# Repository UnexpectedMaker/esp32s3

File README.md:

# Unexpected Maker - ESP32-S3 Boards 

Assorted files for my ESP32-S3 development boards 

You can find out more about my ESP32-S3 boards at https://esp32s3.com 

# Contents
In this repo you'll find the following items:

## 3D Models
3D STEP files for each of the OMGS3, NanoS3, TinyS3, ProS3 and FeatherS3 boards

## KiCAD 6/7/8 Symbols
KiCAD 6 symbol files for each of the boards that you can use when integrating one of them into one of your PCB designs.
NanoS3 symbol file is for KiCAD 7 or later
OMGS3 symbol file is for KiCAD 8 or later

## KiCAD 6/7 Footprints	
KiCAD 6 footprint files for each of the boards including both SMD and TH versions for the ProS3
NanoS3 footprint file is for KiCAD 7 or later
OMGS3 footprint file is for KiCAD 8 or later

## Schematics
PDF Schematics for each of the OMGS3, NanoS3, TinyS3, ProS3 and FeatherS3 boards

## Pin Reference Cards
Hires pinout reference cards for each of the OMGS3, NanoS3, TinyS3, ProS3 and FeatherS3 boards

# Support Unexpected Maker

I love designing, making, and releasing projects and products that empower others to learn and build amazing things! I do it because I believe it’s important to share knowledge and give back to the community as many have done before me. It helps us all learn and grow.

Please consider supporting me by buying some of my products from:

https://unexpectedmaker.com/shop

Or by buying one of my products on tindie or Lectronz:

https://www.tindie.com/stores/seonr/
https://lectronz.com/stores/unexpectedmaker

Or by becoming a Patron:

https://www.patreon.com/unexpectedmaker

## Unexpected Maker
http://youtube.com/c/unexpectedmaker

http://twitter.com/unexpectedmaker

https://discord.gg/xAHpApP

https://www.facebook.com/unexpectedmaker/

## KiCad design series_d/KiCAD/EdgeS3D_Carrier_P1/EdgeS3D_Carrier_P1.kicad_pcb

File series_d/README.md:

# Unexpected Maker - Series[D]

Assorted files for my new ESP32-S3 Series[D] development boards 

You can find out more about my ESP32-S3 boards at https://esp32s3.com

# Contents
In this repo you'll find the following items:

## 3D Models
3D STEP files for each of the TinyS3[D], ProS3[D], FeatherS3[D] and EdgeS3[D] boards

You'll also find a STEP file for the EdgeS3[D] Reference Carrier board and a STEP for the M.2 connector footprint with the EdgeS3[D] inserted to help line things up.

## Schematics
PDF Schematics for each of the TinyS3[D], ProS3[D], FeatherS3[D] and EdgeS3[D] boards.

## KiCAD (v9)
Symbol and Footprint for EdgeS3[D] and a project folder for the EdgeS3[D] Reference Carrier PCB.

## Pin Reference Cards
Hires pinout reference cards for each of the TinyS3[D], ProS3[D], FeatherS3[D] and EdgeS3[D] boards

# Support Unexpected Maker
I love designing, making, and releasing projects and products that empower others to learn and build amazing things! I do it because I believe it’s important to share knowledge and give back to the community as many have done before me. It helps us all learn and grow.

Please consider supporting me by buying some of my products from:

https://unexpectedmaker.com/shop

Or by buying one of my products on tindie or Lectronz:

https://www.tindie.com/stores/seonr/
https://lectronz.com/stores/unexpectedmaker

Or by becoming a Patron:

https://www.patreon.com/unexpectedmaker

## Unexpected Maker
http://youtube.com/c/unexpectedmaker

http://twitter.com/unexpectedmaker

https://discord.gg/xAHpApP

https://www.facebook.com/unexpectedmaker/

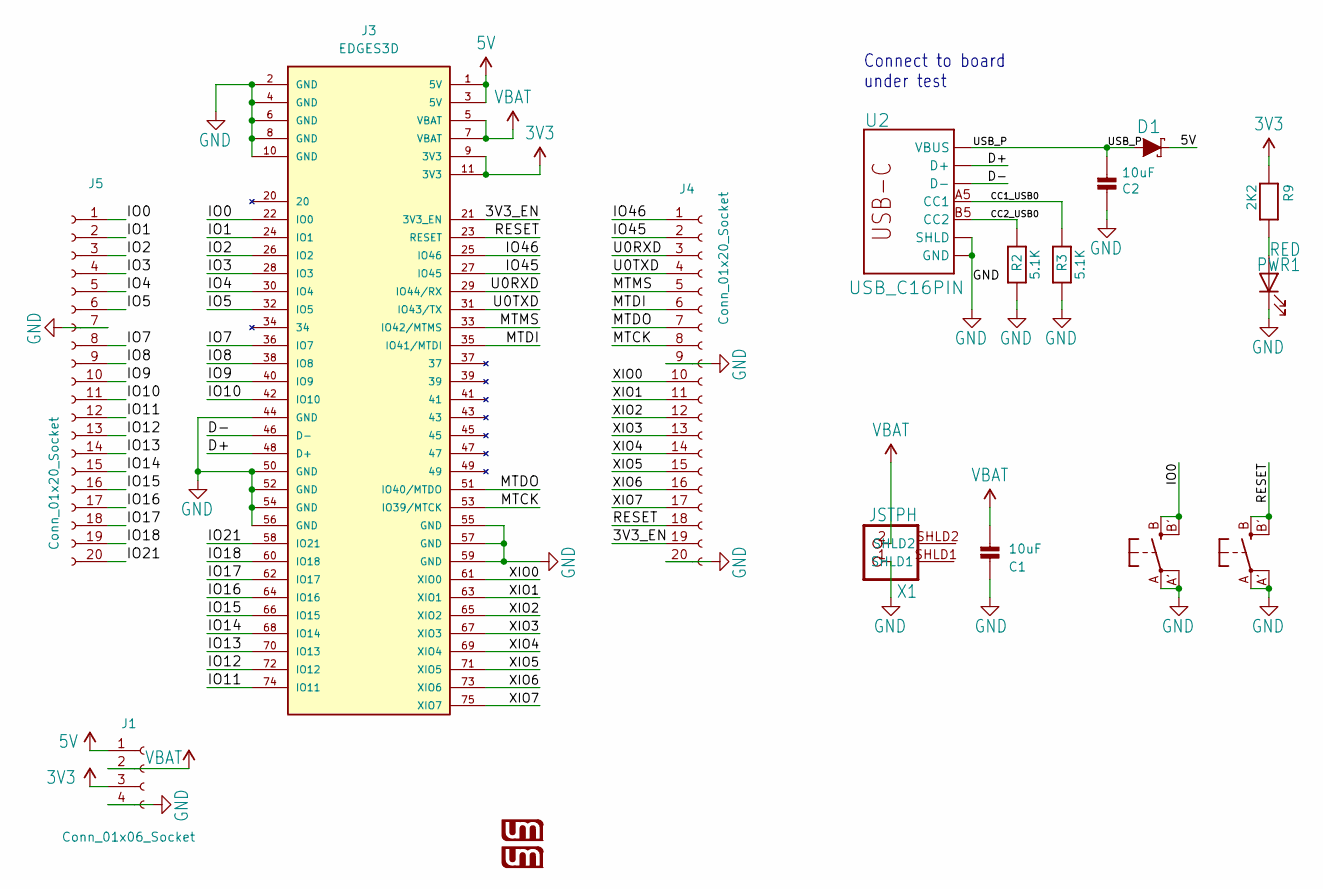
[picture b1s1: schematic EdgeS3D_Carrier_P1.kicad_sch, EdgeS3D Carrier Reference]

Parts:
C1, C2: 10uF; C_0603_1608Metric
D1: DIODE-SCHOTTKYWIDE; SOD-523-MSK4010
J1: Conn_01x06_Socket; PinHeader_1x04_P2.54mm_Vertical
J3: EDGES3D; AMPHENOL_MDT275B03001; PARTREV 7
J4, J5: Conn_01x20_Socket; PinHeader_1x20_P2.54mm_Vertical
PWR1: RED; LED_0805_2012Metric
R2, R3: 5.1K; R_0402_1005Metric
R9: 2K2; _0805MP
SW1, SW2: KMR2; BTN_KMR2_4.6X2.8
U2: USB_C16PIN; USB-C-16P-LESSPASTE-2-FIxed
U$1, U$2: UM_LOGONEW_SMALL; UM_LOGO_NEW_SMALL
X1: JSTPH; JST-PICOBLADE

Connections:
3V3: J1.3, J3.9 (3V3), J3.11 (3V3), R9.1
5V: D1.C, J1.1, J3.1 (5V), J3.3 (5V)
/3V3_EN: J3.21 (3V3_EN), J4.19
/CC1_USB0: R3.2, U2.A5 (CC1)
/CC2_USB0: R2.2, U2.B5 (CC2)
/D+: J3.48 (D+), U2.A6 (D+), U2.B6 (D+)
/D-: J3.46 (D-), U2.A7 (D-), U2.B7 (D-)
/IO0: J3.22 (IO0), J5.1, SW1.B (S), SW1.B' (S1)
/IO1: J3.24 (IO1), J5.2
/IO2: J3.26 (IO2), J5.3
/IO3: J3.28 (IO3), J5.4
/IO4: J3.30 (IO4), J5.5
/IO5: J3.32 (IO5), J5.6
/IO7: J3.36 (IO7), J5.8
/IO8: J3.38 (IO8), J5.9
/IO9: J3.40 (IO9), J5.10
/IO10: J3.42 (IO10), J5.11
/IO11: J3.74 (IO11), J5.12
/IO12: J3.72 (IO12), J5.13
/IO13: J3.70 (IO13), J5.14
/IO14: J3.68 (IO14), J5.15
/IO15: J3.66 (IO15), J5.16
/IO16: J3.64 (IO16), J5.17
/IO17: J3.62 (IO17), J5.18
/IO18: J3.60 (IO18), J5.19
/IO21: J3.58 (IO21), J5.20
/IO45: J3.27 (IO45), J4.2
/IO46: J3.25 (IO46), J4.1
/MTCK: J3.53 (IO39/MTCK), J4.8
/MTDI: J3.35 (IO41/MTDI), J4.6
/MTDO: J3.51 (IO40/MTDO), J4.7
/MTMS: J3.33 (IO42/MTMS), J4.5
/RESET: J3.23 (RESET), J4.18, SW2.B (S), SW2.B' (S1)
/U0RXD: J3.29 (IO44/RX), J4.3
/U0TXD: J3.31 (IO43/TX), J4.4
/USB_P: C2.2, D1.A, U2.VBUS1 (VBUS), U2.VBUS2 (VBUS)
/XIO0: J3.61 (XIO0), J4.10
/XIO1: J3.63 (XIO1), J4.11
/XIO2: J3.65 (XIO2), J4.12
/XIO3: J3.67 (XIO3), J4.13
/XIO4: J3.69 (XIO4), J4.14
/XIO5: J3.71 (XIO5), J4.15
/XIO6: J3.73 (XIO6), J4.16
/XIO7: J3.75 (XIO7), J4.17
GND: C1.1, C2.1, J1.4, J3.2 (GND), J3.4 (GND), J3.6 (GND), J3.8 (GND), J3.10 (GND), J3.44 (GND), J3.50 (GND), J3.52 (GND), J3.54 (GND), J3.55 (GND), J3.56 (GND), J3.57 (GND), J3.59 (GND), J4.9, J4.20, J5.7, PWR1.1 (K), R2.1, R3.1, SW1.A, SW1.A' (P1), SW2.A, SW2.A' (P1), U2.GND, U2.GND2 (GND), U2.SHLD, U2.SHLD2 (SHLD), U2.SHLD3 (SHLD), U2.SHLD4 (SHLD), U2.SHLD5 (SHLD), U2.SHLD6 (SHLD), U2.SHLD7 (SHLD), U2.SHLD8 (SHLD), X1.1
unnamed: PWR1.2 (A), R9.2
VBAT: C1.2, J1.2, J3.5 (VBAT), J3.7 (VBAT), X1.2

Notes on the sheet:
Connect to board under test

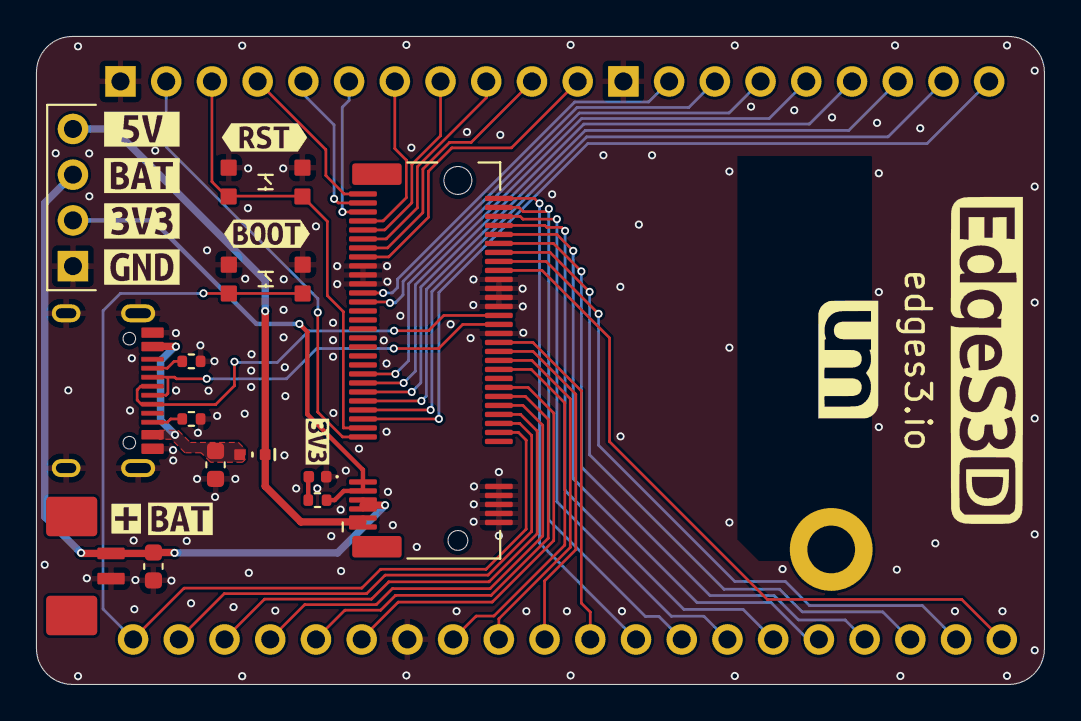
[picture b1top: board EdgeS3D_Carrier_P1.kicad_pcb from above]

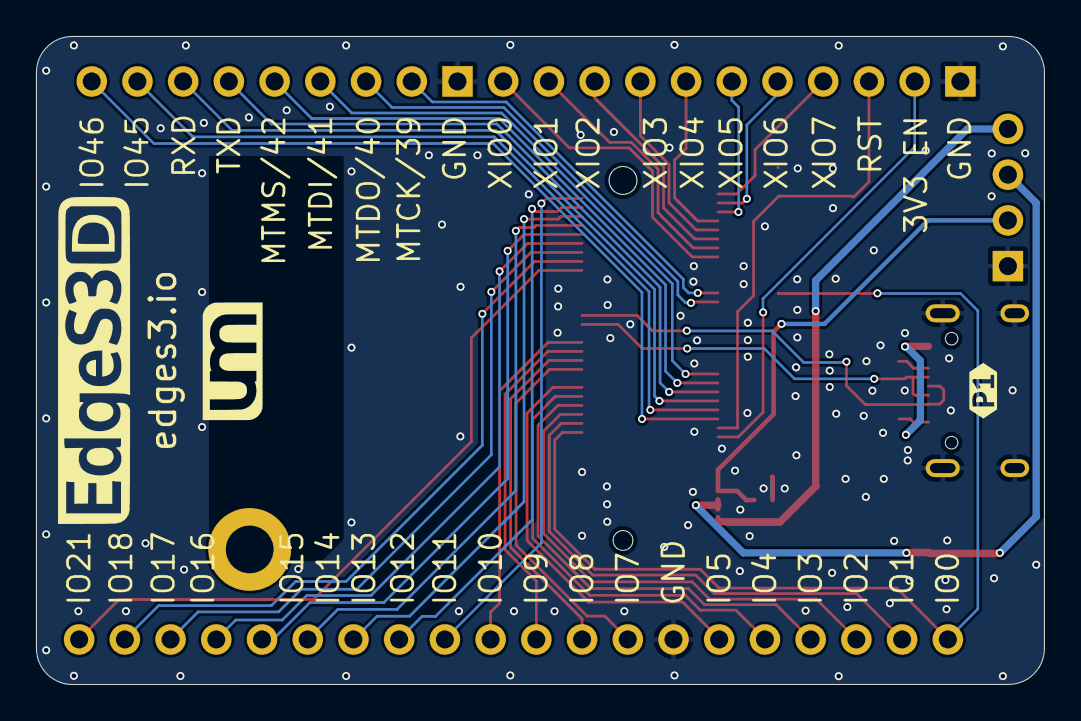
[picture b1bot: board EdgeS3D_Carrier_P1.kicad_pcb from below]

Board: 2 copper layers, 56.0 x 36.0 mm, 27 parts (2 on the bottom side), 47 nets.

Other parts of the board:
kibuzzard-66BFF55A: G***; kibuzzard-66BFF55A
kibuzzard-66BFF56B: G***; kibuzzard-66BFF56B
kibuzzard-66C05786: G***; kibuzzard-66C05786
kibuzzard-6857AC6A: G***; kibuzzard-6857AC6A
kibuzzard-6857AC7B: G***; kibuzzard-6857AC7B
kibuzzard-6857AC8E: G***; kibuzzard-6857AC8E
kibuzzard-6857AC89: G***; kibuzzard-6857AC89
kibuzzard-6857AD16: G***; kibuzzard-6857AD16
kibuzzard-6857ADA7: G***; kibuzzard-6857ADA7
kibuzzard-664315DB: G***; kibuzzard-664315DB

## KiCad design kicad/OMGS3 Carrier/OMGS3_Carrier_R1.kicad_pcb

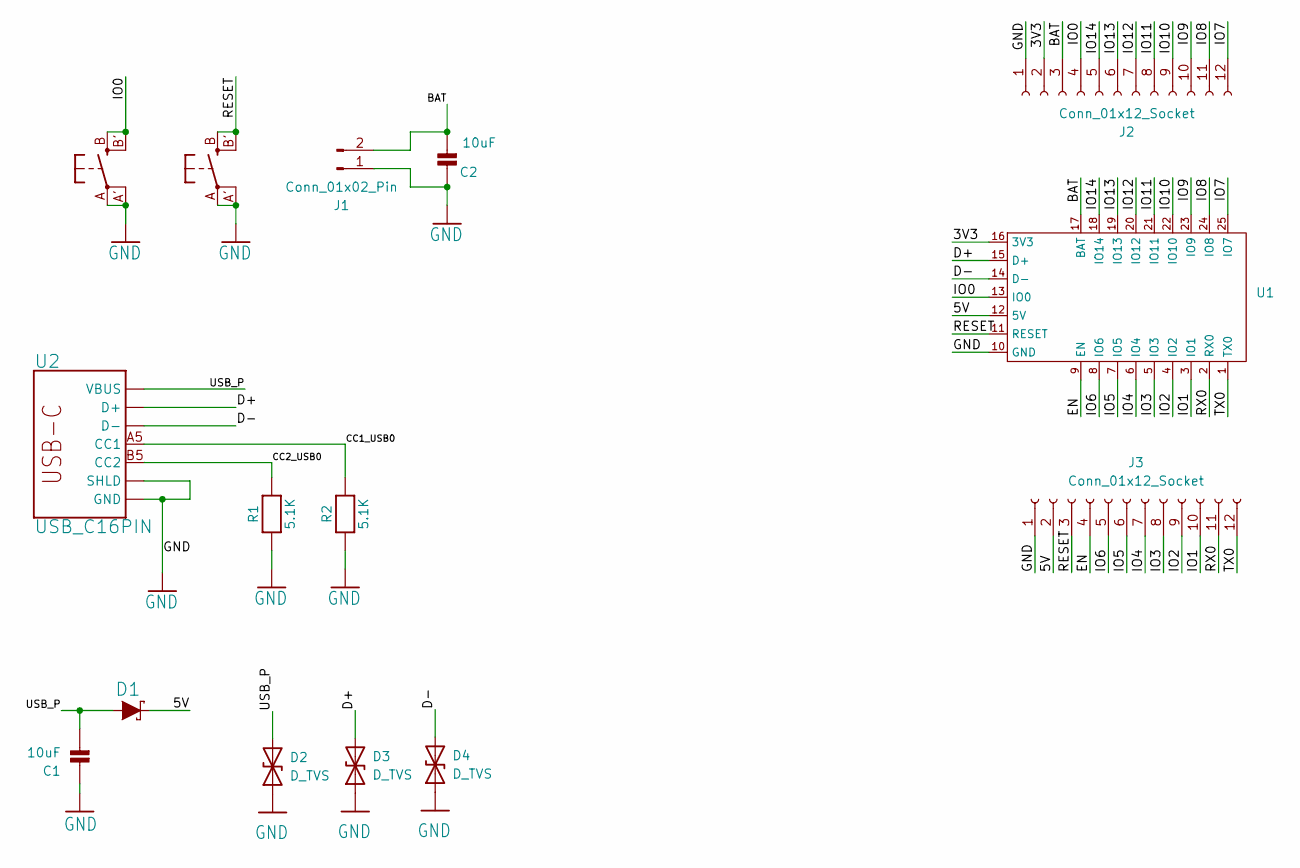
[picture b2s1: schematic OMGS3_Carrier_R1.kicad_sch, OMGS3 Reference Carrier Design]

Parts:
C1, C2: 10uF; C_0603_1608Metric
D1: DIODE-SCHOTTKYWIDE; SOD-523-MSK4010
D2, D3, D4: D_TVS; X1-DFN1006-2
J1: Conn_01x02_Pin; JST-PICOBLADE
J2, J3: Conn_01x12_Socket; PinHeader_1x12_P2.54mm_Vertical
R1, R2: 5.1K; R_0402_1005Metric
SW1, SW2: KMR2; BTN_KMR2_4.6X2.8
U1: OMGS3
U2: USB_C16PIN; USB-C-16P-LESSPASTE-2-Fixed-Sqr-Front

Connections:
/3V3: J2.2, U1.16 (3V3)
/5V: D1.C, J3.2, U1.12 (5V)
/BAT: C2.2, J1.2, J2.3, U1.17 (BAT)
/CC1_USB0: R2.2, U2.A5 (CC1)
/CC2_USB0: R1.2, U2.B5 (CC2)
/D+: D3.2 (A2), U1.15 (D+), U2.A6 (D+), U2.B6 (D+)
/D-: D4.2 (A2), U1.14 (D-), U2.A7 (D-), U2.B7 (D-)
/EN: J3.4, U1.9 (EN)
/IO0: J2.4, SW1.B (S), SW1.B' (S1), U1.13 (IO0)
/IO1: J3.10, U1.3 (IO1)
/IO2: J3.9, U1.4 (IO2)
/IO3: J3.8, U1.5 (IO3)
/IO4: J3.7, U1.6 (IO4)
/IO5: J3.6, U1.7 (IO5)
/IO6: J3.5, U1.8 (IO6)
/IO7: J2.12, U1.25 (IO7)
/IO8: J2.11, U1.24 (IO8)
/IO9: J2.10, U1.23 (IO9)
/IO10: J2.9, U1.22 (IO10)
/IO11: J2.8, U1.21 (IO11)
/IO12: J2.7, U1.20 (IO12)
/IO13: J2.6, U1.19 (IO13)
/IO14: J2.5, U1.18 (IO14)
/RESET: J3.3, SW2.B (S), SW2.B' (S1), U1.11 (RESET)
/RX0: J3.11, U1.2 (RX0)
/TX0: J3.12, U1.1 (TX0)
/USB_P: C1.2, D1.A, D2.2 (A2), U2.VBUS1 (VBUS), U2.VBUS2 (VBUS)
GND: C1.1, C2.1, D2.1 (A1), D3.1 (A1), D4.1 (A1), J1.1, J2.1, J3.1, R1.1, R2.1, SW1.A, SW1.A' (P1), SW2.A, SW2.A' (P1), U1.10 (GND), U1.EXP, U2.GND, U2.GND2 (GND), U2.SHLD, U2.SHLD1 (SHLD), U2.SHLD2 (SHLD), U2.SHLD3 (SHLD), U2.SHLD4 (SHLD), U2.SHLD5 (SHLD), U2.SHLD6 (SHLD), U2.SHLD7 (SHLD), U2.SHLD8 (SHLD)

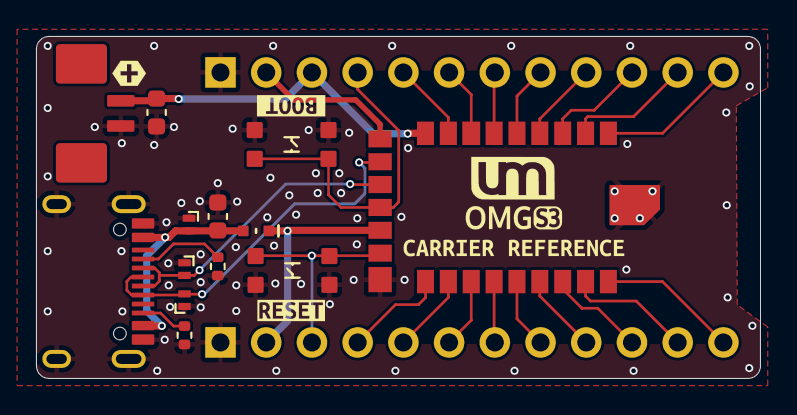
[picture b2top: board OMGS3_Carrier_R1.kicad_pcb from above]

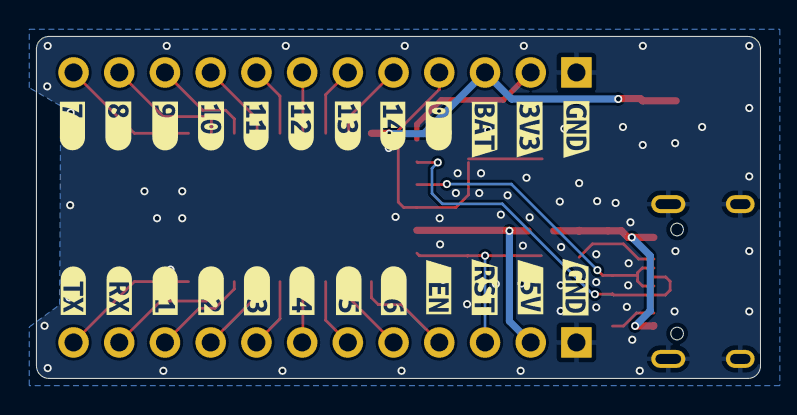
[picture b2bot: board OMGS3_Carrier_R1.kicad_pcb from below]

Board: 2 copper layers, 40.2 x 19.0 mm, 43 parts (24 on the bottom side), 28 nets.

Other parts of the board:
kibuzzard-66A337D7: G***; kibuzzard-66A337D7
kibuzzard-66A3379E: G***; kibuzzard-66A3379E
kibuzzard-66BFF9CC: G***; kibuzzard-66BFF9CC
kibuzzard-66BFF9DF: G***; kibuzzard-66BFF9DF
kibuzzard-66BFF9E6: G***; kibuzzard-66BFF9E6
kibuzzard-66BFF9F3: G***; kibuzzard-66BFF9F3
kibuzzard-66BFF9F9: G***; kibuzzard-66BFF9F9
kibuzzard-66BFF9FE: G***; kibuzzard-66BFF9FE
kibuzzard-66BFFA1D: G***; kibuzzard-66BFFA1D
kibuzzard-66BFFA03: G***; kibuzzard-66BFFA03
kibuzzard-66BFFA07: G***; kibuzzard-66BFFA07
kibuzzard-66BFFA15: G***; kibuzzard-66BFFA15
kibuzzard-66BFFA19: G***; kibuzzard-66BFFA19
kibuzzard-66BFFA21: G***; kibuzzard-66BFFA21
kibuzzard-66BFFAE0: G***; kibuzzard-66BFFAE0
kibuzzard-66BFFAF9: G***; kibuzzard-66BFFAF9
kibuzzard-66BFFB0C: G***; kibuzzard-66BFFB0C
kibuzzard-66BFFB4C: G***; kibuzzard-66BFFB4C
kibuzzard-66BFFB4F: G***; kibuzzard-66BFFB4F
kibuzzard-66BFFB5D: G***; kibuzzard-66BFFB5D
kibuzzard-66BFFB12: G***; kibuzzard-66BFFB12
kibuzzard-66BFFB21: G***; kibuzzard-66BFFB21
kibuzzard-66BFFB47: G***; kibuzzard-66BFFB47
kibuzzard-66BFFB52: G***; kibuzzard-66BFFB52
kibuzzard-66BFFB54: G***; kibuzzard-66BFFB54
kibuzzard-66BFFB58: G***; kibuzzard-66BFFB58
kibuzzard-66C531C2: G***; kibuzzard-66C531C2
kibuzzard-66C53217: G***; kibuzzard-66C53217

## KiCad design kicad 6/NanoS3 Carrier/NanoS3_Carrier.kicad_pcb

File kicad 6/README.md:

# KiCAD Footprints - Unexpected Maker - ESP32-S3 Boards 
KiCAD Footprints for my ESP32-S3 boards  

You can find out more about my ESP32-S3 boards at https://esp32s3.com 

Please refer to the included license.

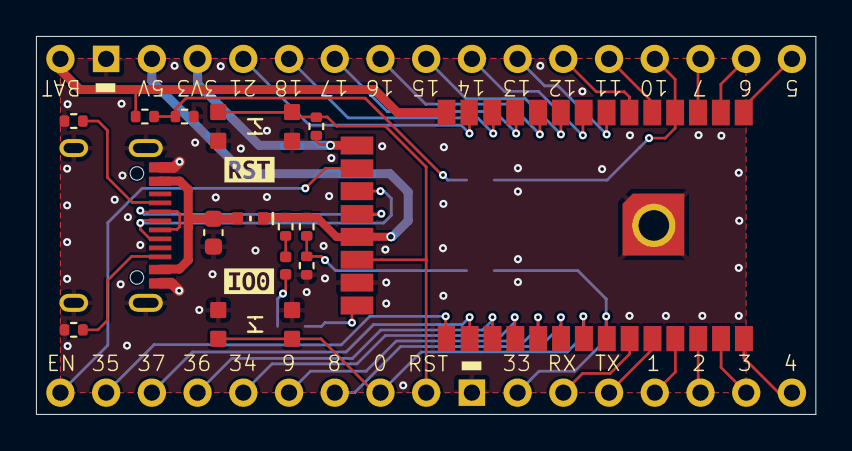
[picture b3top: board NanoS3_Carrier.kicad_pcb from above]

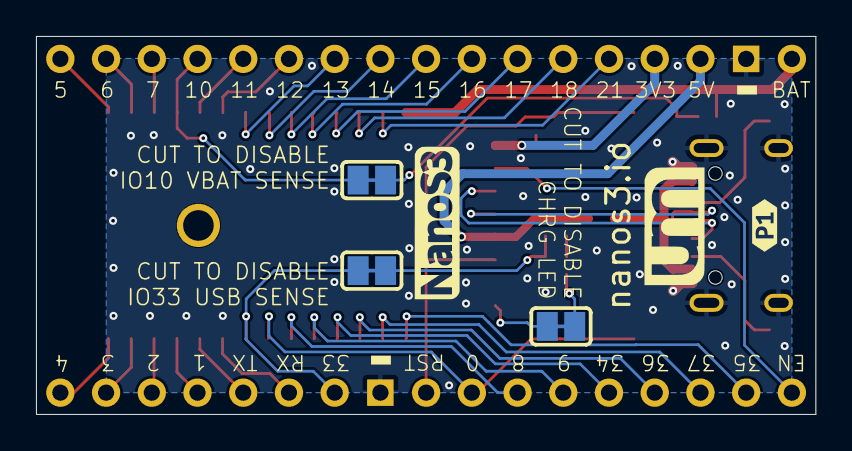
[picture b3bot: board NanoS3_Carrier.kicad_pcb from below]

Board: 2 copper layers, 43.3 x 21.0 mm, 24 parts (5 on the bottom side), 43 nets.

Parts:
A1, A2, A3: SOLDERJUMPERCLOSED; SOLDERJUMPER_CLOSEDWIRE
C1: C_Small; C_0603_1608Metric
D3: ORANGE; LED_0402_1005Metric
D5: DIODE-SCHOTTKYWIDE; SOD-523-MSK4010
J2: USB_C; USB-C-16P-LESSPASTE-2-FIxed
J4, J5: Conn_01x17_Pin; 1X17_BLIZZARD_S3_BOTTOM
R1: 2K; R_0402_1005Metric
R2: 2K2; R_0402_1005Metric
R3: 3K3; R_0402_1005Metric
R6: 442K; R_0402_1005Metric
R7: 160K; R_0402_1005Metric
R9, R11: 5.1K; R_0402_1005Metric
R14: 10K; R_0402_1005Metric
SW1, SW2: SWITCH_TACT_SMT4.6X2.8; BTN_KMR2_4.6X2.8
U1: NanoS3; NanoS3_HandSolder
U$88: UM_LOGONEW_SMALLER; UM_LOGO_NEW_SMALL
kibuzzard-649F567F: G***; kibuzzard-649F567F
kibuzzard-649F677A: G***; kibuzzard-649F677A
kibuzzard-649F5696: G***; kibuzzard-649F5696

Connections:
3.3V: J4.4, R14.2, U1.8 (3v3)
/CC1: J2.A5 (CC1), R11.2
/CC2: J2.B5 (CC2), R9.2
/D+: J2.A6 (D+), J2.B6 (D+), U1.6 (D+)
/D-: J2.A7 (D-), J2.B7 (D-), U1.5 (D-)
/EN: J5.1, U1.7 (EN)
/IO0: J5.8, SW2.A, SW2.A' (P1), U1.29 (IO0)
/IO1: J5.14, U1.33 (IO1)
/IO2: J5.15, U1.34 (IO2)
/IO3: J5.16, U1.35 (IO3)
/IO4: J5.17, U1.36 (IO4)
/IO5: J4.17, U1.22 (IO5)
/IO6: J4.16, U1.21 (IO6)
/IO7: J4.15, U1.20 (IO7)
/IO8: J5.7, U1.28 (IO8)
/IO9: J5.6, U1.27 (IO9)
/IO10: A2.1, J4.14, U1.19 (IO10)
/IO10_JUMPER: A2.2, R6.2, R7.1
/IO11: J4.13, U1.18 (IO11)
/IO12: J4.12, U1.17 (IO12)
/IO13: J4.11, U1.16 (IO13)
/IO14: J4.10, U1.15 (IO14)
/IO15: J4.9, U1.14 (IO15)
/IO16: J4.8, U1.13 (IO16)
/IO17: J4.7, U1.12 (IO17)
/IO18: J4.6, U1.11 (IO18)
/IO21: J4.5, U1.10 (IO21)
/IO33: A1.1, J5.11, U1.30 (IO33)
/IO33_JUMPER: A1.2, R2.2, R3.1
/IO34: J5.5, U1.26 (IO34)
/IO35: J5.2, U1.23 (IO35)
/IO36: J5.4, U1.25 (IO36)
/IO37: J5.3, U1.24 (IO37)
/RESET: J5.9, R14.1, SW1.A, SW1.A' (P1), U1.3 (RESET)
/RX: J5.12, U1.31 (RX)
/STAT: A3.2, U1.1 (STAT)
/STAT_JUMPER: A3.1, D3.2
/TX: J5.13, U1.32 (TX)
/USB: D5.C, J4.3, R1.1, R2.1, U1.4 (5V)
/USB_P: C1.2, D5.A, J2.VBUS1 (VBUS), J2.VBUS2 (VBUS)
GND: C1.1, J2.GND, J2.GND2 (GND), J2.SHLD1 (SHLD), J2.SHLD2 (SHLD), J2.SHLD3 (SHLD), J2.SHLD4 (SHLD), J4.2, J5.10, R3.2, R7.2, R9.1, R11.1, SW1.B (S), SW1.B' (S1), SW2.B (S), SW2.B' (S1), U1.2 (GND)
unnamed: D3.1, R1.2
VBAT: J4.1, R6.1, U1.9 (VBAT)

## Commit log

2022-01-30 Initial content commit
2022-02-02 Updated MicroPython firmware as at Feb 2nd, 20212 Added helper libraries and example code for MicroPython
2022-02-03 Fixed some typos, thanks @mcauser
2022-02-26 Neopixels are GRB order
2022-02-28 update get_battery_voltage with clear calculation
2022-03-15 Added newer MicroPython nightly builds and removed older ones
2022-04-23 Updated FeatherS3 pinout card to latest version
2022-04-24 RGB-Blink sample
2022-04-24 RGB-Blink sample for all 3 boards
2022-04-24 RGB-Blink brightness
2022-04-25 README files added
2022-04-25 Rainbox ColorWheel sample
2022-04-28 Added link to the Arduino Helper Library repository
2022-05-23 Fixed ProS3 symbol pin orientations
2022-08-06 Updated ProS3 and FeatherS3 schematics, fixing vertical STEMMA connector pin names
2022-08-06 Fixed STEMMA/QT signal orientation to stop confusing people :)
2022-08-17 Updated readme and removed old MP 1.18 firmware
2022-09-21 Update README.md
    Fixed incorrect examples URL
2022-12-24 Fixed incorrectly rotated pins on the TinyS3 and FeatherS3 KiCAD Symbol
2023-01-14 Update README.md
    added exact helper library name
2023-03-01 Updated ProS3 Symbol with aligned pins for better grid mapping
2023-03-11 Updated FeatherS3 schematic for P7 to show new IO pins for I2C bus 2 on the vertical STEMMA/QT connector
2023-07-26 Added KiCAD 7 Footprint and Symbol for NanoS3
2023-07-26 Added KiCAD 7 NanoS3 Carrier Design Files
2023-07-27 Added NanoS3 Schematic
2023-07-29 Fixed incorrect NanoS3 KiCAD Symbol and added missing pinout card
2023-08-02 Updated TinyS3 models
2023-08-02 Updated other ESP32-S3 models
2023-08-02 Readme changes
2023-08-02 Updated kicad folder
2023-08-02 making images smaller
2023-08-02 make images smaller
2023-08-26 Updated pinout cards and added uFL versions
2024-02-08 Updated FeatherS3 pinout cards to include ADC info for VBAT Sense and AMB Light Sensor
2024-03-18 Fixed grid spacing for KiCAD Symbols
2024-06-06 Added FeatherS3 Neo files
2024-06-06 Fixed FeatherS3 Neo schematic name
2024-06-06 Adding missing FeatherS3 Neo pinout card
2024-06-30 Updated NanoS3 schematic to correct version
2024-07-04 Added PlatformIO example project for FeatherS3 and updated readme
2024-08-18 Added OMGS3 files Added missing NanoS3 CP shipping files
2024-09-07 Updated OMGS3 KiCAD Symbol and Footprint
2024-09-10 Added OMGS3 Carrier KiCAD Project Added STEP files for OMGUSB and OMG Carrier
2024-09-15 Updated OMGS3 pinout card
2025-07-11 Added new Series[D] content
2025-07-12 Added EdgeS3[D] carrier reference kicad project and STEP file Updated EdgeS3[D] footprint and readme
2025-07-14 Added code folder with link to Arduino Series[D] helper Added CircuitPython shipping files
2025-07-15 Updated readme with more info and updated EdgeS3D.kicad_mod
2025-07-26 Fixed some wrong file names and updated NanoS3 Step
2025-10-06 Update platformio.ini
    Updated to use pioarduino to get latest ESP32 Arduino Core 3.x
2025-10-17 Added FeatherS3 P8 schematic
